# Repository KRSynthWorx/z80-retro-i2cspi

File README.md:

# [Z80-Retro!](https://github.com/johnwinans/2063-Z80) I2C/SPI Master Interface Board & Driver Library

An addon I2C/SPI master interface board that uses the [Z80-Retro!](https://github.com/johnwinans/2063-Z80)
parallel printer port and a bit-banged driver library to interact
with the I2C/SPI ports. KiCad design files are also included.

## Description

### Driver Library
[i2cspi_lib.asm](src/i2cspi_lib.asm) -
This driver library includes all necessary routines to communicate with I2C and SPI hardware devices
using the Z80-Retro! parallel port. Extensive comments and protocol descriptions are provided
to help understand the library. The library requires the [retromon.sym](https://github.com/KRSynthWorx/z80-retro-monitor/blob/main/src/retromon.sym)
symbol table from the [z80-retro-monitor](https://github.com/KRSynthWorx/z80-retro-monitor) project.

### PCB Hardware
An I2C/SPI master interface board using bit-bang techniques and utilizes the Z80-Retro!
parallel printer port. The PCB design includes 4 I2C ports and 4 SPI ports. The I2C
ports are all common and the SPI ports include 4 individual chip select (CS) lines.
Requires +5vdc be connected from the Z80-Retro! or an external power supply.

* A PDF version of the schematic can be found [here](kicad/i2c-adapter-schematic.pdf).
* Build of Materals (aka BOM) can be found [here](kicad/bom/ibom.html).

### PCB Layout

---

### I2C Timing Capture

---

### SPI Timing Capture

## Help

### Library Common Routines

```ACTIVE_LED``` - Set the ACTIVE LED on the I2C/SPI interface board on or off  

---

### I2C Routines

```I2C_INIT``` - Initialize I2C status variables and the Z80-Retro! PRN_DAT port  
```I2C_START``` - Initiate I2C communication with a START condition  
```I2C_STOP``` - Stop I2C communication with a STOP condition  
```I2C_SEND_BIT``` - Send a bit over the I2C bus  
```I2C_READ_BIT``` - Read a bit on the I2C bus  
```I2C_SEND_BYTE``` - Send a byte to the I2C bus  
```I2C_READ_BYTE``` - Read a byte from the I2C bus  
```I2C_SEND_STREAM``` - Send a byte stream to the I2C bus  
```I2C_READ_STREAM``` - Read a byte stream from the I2C bus  

---

### SPI Routines

```SPI_INIT```- Initialize the SPI MODE, bit transfer order and the Z80-Retro! PRN_DAT port  
```SPI_SEND_BYTE``` - Send 8 bits to the SPI port and discard the received data  
```SPI_READ_BYTE``` - Read 8 bits from the SPI port  
```SPI_CSx_TRUE``` - Assert the select line initialized in SPI_INIT (CS1 - CS4) supported  
```SPI_CSx_FALSE``` - De-assert the select line initialized in SPI_INIT (CS1 - CS4) supported  
```SPI_SEND_STREAM``` - Send a stream of bytes to the SPI port  
```SPI_READ_STREAM``` - Read a stream of bytes from the SPI port  

---

Several example routines are included to test the various functions. Everything is heavily
commented explaining the library routines and how to use them. These include:
- [ad_test.asm](src/ad_test.asm) - test a NXP Semiconductors PCF8591 I2C A/D-D/A converter
- [eeprom_test.asm](src/eeprom_test.asm) - test a generic 24C256 I2C EEPROM
- [gpio_test.asm](src/gpio_test.asm) - test a NXP Semiconductors PCF8574 I2C 8-bit GPIO expander
- [led_test.asm](src/led_test.asm) - test an Analog Devices MAX7219 LED driver in SPI mode 0
- [oled_test.asm](src/oled_test.asm) - test a generic SSD1306 128x64 SPI 0.96" OLED display
- [spi_test.asm](src/spi_test.asm) - test an Analog Devices ADXL345 accelerometer in SPI mode 3

## Author

[Kenny Maytum](mailto:ken_m@comcast.net) - KRSynthWorx

## Version History

* v1.0 - Driver Library
	* Initial Public Release
* v2.0 - KiCad Design Files
	* Initial Public Release

## License

This project is licensed under the [GNU Lesser General Public License] - see the LICENSE file for details

## Acknowledgments

Inspiration, code snippets, libraries, etc.
* [John's Basement YouTube Channel](https://www.youtube.com/c/JohnsBasement)
* [John Winans](https://github.com/johnwinans)
* [K. S. Jiang](https://github.com/ksjiang/bb85)
* [I2C Bus](https://i2c-bus.org)
* [SPI Bus](https://www.corelis.com/education/tutorials/spi-tutorial)

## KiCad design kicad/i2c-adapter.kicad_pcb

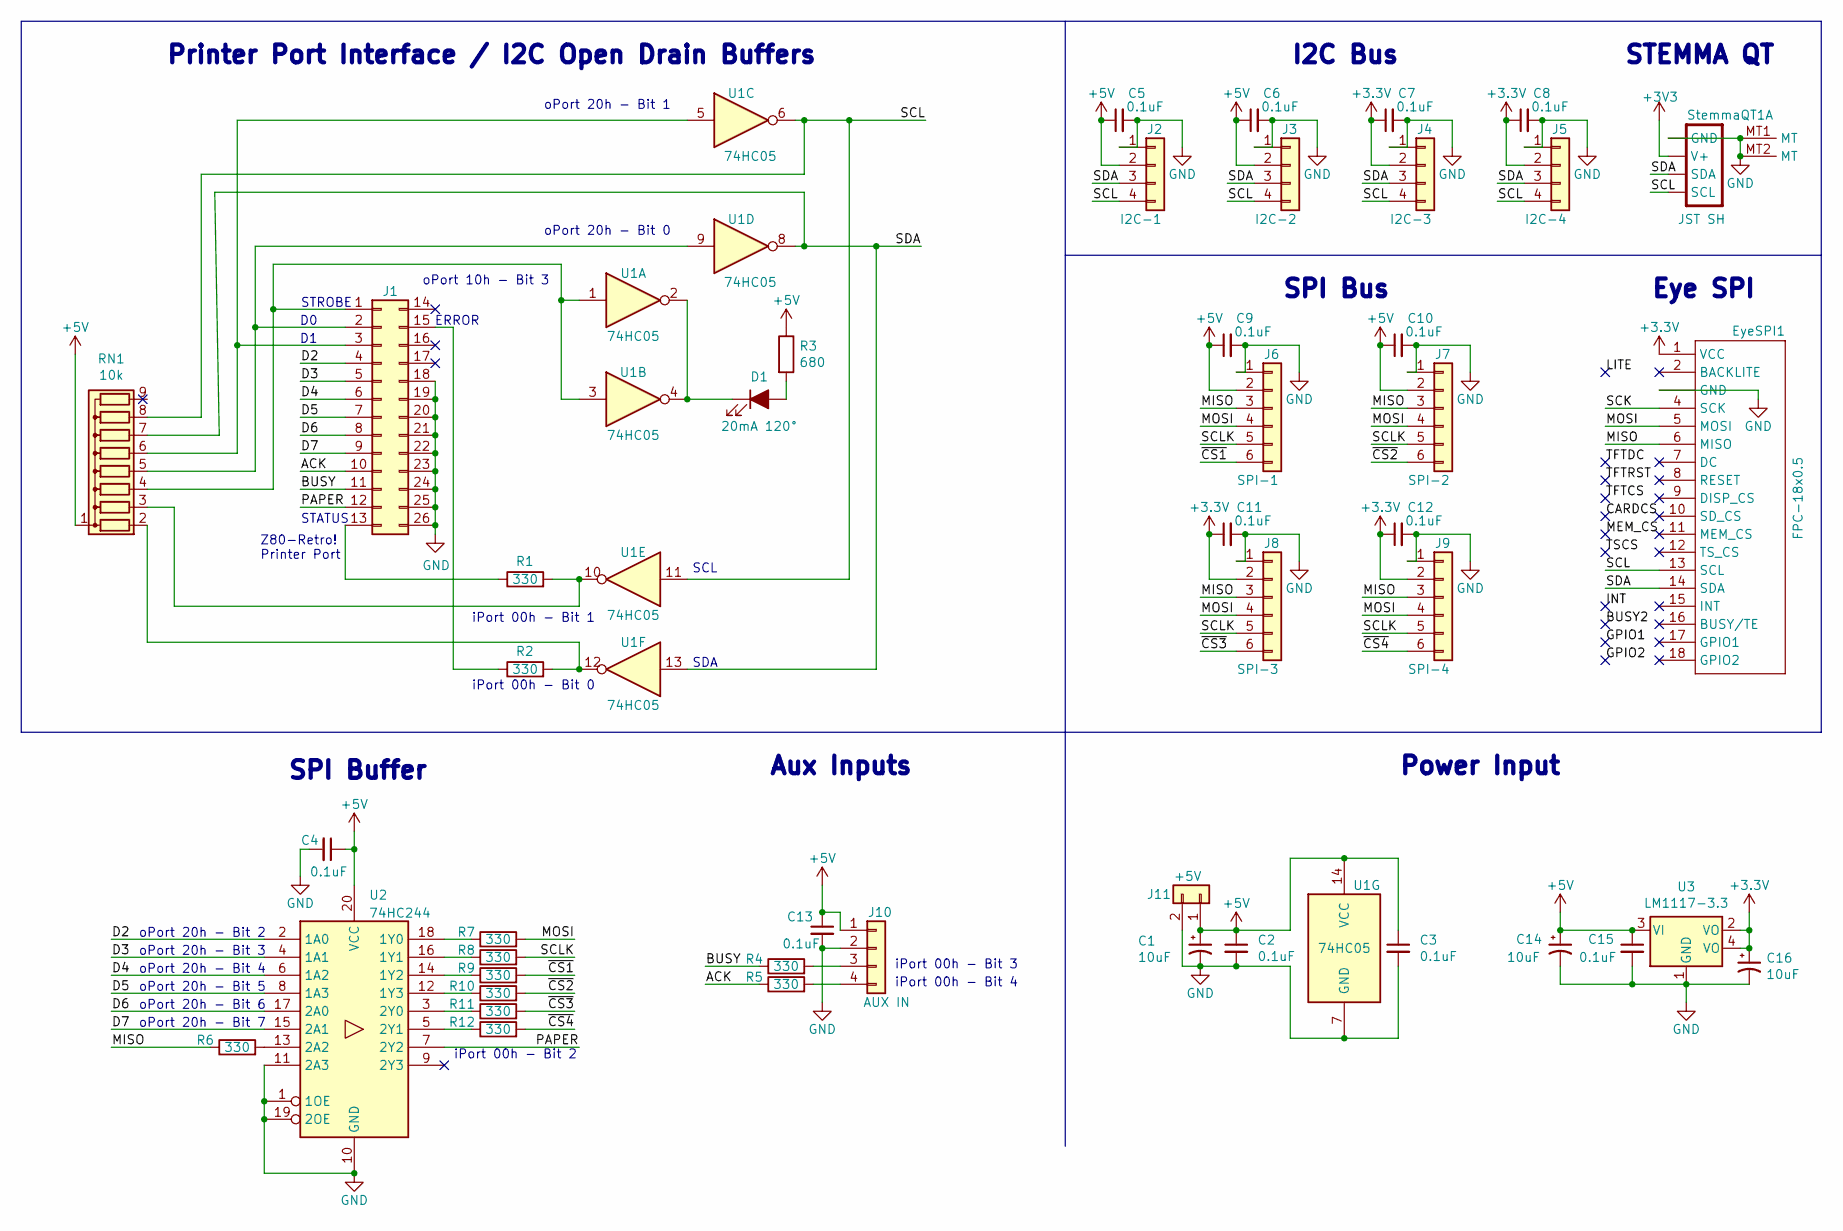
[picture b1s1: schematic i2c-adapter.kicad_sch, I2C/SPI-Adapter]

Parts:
C1: 10uF; CP_EIA-3216-10_Kemet-I_Pad1.58x1.35mm_HandSolder; LCSC C15850
C2, C3, C4, C5, C6, C7, C8, C9, C10, C11, C12, C13: 0.1uF; C_0805_2012Metric_Pad1.18x1.45mm_HandSolder; LCSC C28233
C14: 10uF; CP_EIA-3216-10_Kemet-I_Pad1.58x1.35mm_HandSolder; MPN ECE-A1EKS100; Digi-Key_PN P975-ND
C15: 0.1uF; C_0805_2012Metric_Pad1.18x1.45mm_HandSolder; MPN CL10B104KB8NNWC; Digi-Key_PN 1276-1935-1-ND
C16: 10uF; CP_EIA-3216-10_Kemet-I_Pad1.58x1.35mm_HandSolder; MPN CL21A106MQFNNNE; Digi-Key_PN 1276-1298-1-ND
D1: 20mA 120°; LED_0805_2012Metric_Pad1.15x1.40mm_HandSolder; LCSC C375546
EyeSPI1: FPC-18x0.5; EYE_SPI_DISPLAY_BOTCONTACT; LCSC C2856802
J1: Conn_02x13_Top_Bottom; PinSocket_2x13_P2.54mm_Vertical
J2: I2C-1; PinSocket_1x04_P2.54mm_Vertical
J3: I2C-2; PinSocket_1x04_P2.54mm_Vertical
J4: I2C-3; PinSocket_1x04_P2.54mm_Vertical
J5: I2C-4; PinSocket_1x04_P2.54mm_Vertical
J6: SPI-1; PinSocket_1x06_P2.54mm_Vertical
J7: SPI-2; PinSocket_1x06_P2.54mm_Vertical
J8: SPI-3; PinSocket_1x06_P2.54mm_Vertical
J9: SPI-4; PinSocket_1x06_P2.54mm_Vertical
J10: AUX IN; PinHeader_1x04_P2.54mm_Vertical
J11: +5V; PinHeader_1x02_P2.54mm_Vertical
R1, R2, R4, R5, R6, R7, R8, R9, R10, R11, R12: 330; R_0805_2012Metric_Pad1.20x1.40mm_HandSolder; LCSC C17630
R3: 680; R_0805_2012Metric_Pad1.20x1.40mm_HandSolder; LCSC C17798
RN1: 10k; R_Array_SIP9
StemmaQT1: JST SH; JST_SH4; LCSC C145956
U1: 74HC05; DIP-14_W7.62mm_Socket
U2: 74HC244; DIP-20_W7.62mm_Socket
U3: LM1117-3.3; SOT-223; MPN NCP1117ST33T3G; Digi-Key_PN NCP1117ST33T3GOSCT-ND

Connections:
+5V: C1.1, C2.1, C3.1, C4.1, C5.1, C6.1, C9.1, C10.1, C13.1, C14.1, C15.1, J2.2, J3.2, J6.2, J7.2, J10.1, J11.1, R3.1, RN1.1 (common), U1.14 (VCC), U2.20 (VCC), U3.3 (VI)
/ACK: J1.10, R5.1
/BUSY: J1.11, R4.1
/D2: J1.4, U2.2 (1A0)
/D3: J1.5, U2.4 (1A1)
/D4: J1.6, U2.6 (1A2)
/D5: J1.7, U2.8 (1A3)
/D6: J1.8, U2.17 (2A0)
/D7: J1.9, U2.15 (2A1)
/MISO: EyeSPI1.6 (MISO), J6.3, J7.3, J8.3, J9.3, R6.1
/MOSI: EyeSPI1.5 (MOSI), J6.4, J7.4, J8.4, J9.4, R7.2
/PAPER: J1.12, U2.7 (2Y2)
/SCK: EyeSPI1.4 (SCK)
/SCL: EyeSPI1.13 (SCL), J2.4, J3.4, J4.4, J5.4, RN1.8 (R7), StemmaQT1.4 (SCL), U1.6, U1.11
/SCLK: J6.5, J7.5, J8.5, J9.5, R8.2
/SDA: EyeSPI1.14 (SDA), J2.3, J3.3, J4.3, J5.3, RN1.7 (R6), StemmaQT1.3 (SDA), U1.8, U1.13
/~CS1: J6.6, R9.2
/~CS2: J7.6, R10.2
/~CS3: J8.6, R11.2
/~CS4: J9.6, R12.2
GND: C1.2, C2.2, C3.2, C4.2, C5.2, C6.2, C7.2, C8.2, C9.2, C10.2, C11.2, C12.2, C13.2, C14.2, C15.2, C16.2, EyeSPI1.3 (GND), EyeSPI1.SUPPORT1 (GND), EyeSPI1.SUPPORT2 (GND), J1.18, J1.19, J1.20, J1.21, J1.22, J1.23, J1.24, J1.25, J1.26, J2.1, J3.1, J4.1, J5.1, J6.1, J7.1, J8.1, J9.1, J10.2, J11.2, StemmaQT1.1 (GND), StemmaQT1.MT1 (MT), StemmaQT1.MT2 (MT), U1.7 (GND), U2.1 (1OE), U2.10 (GND), U2.11 (2A3), U2.19 (2OE), U3.1 (GND)
unnamed: D1.1 (K), U1.2, U1.4
unnamed: D1.2 (A), R3.2
unnamed: J1.1, RN1.4 (R3), U1.1, U1.3
unnamed: J1.2, RN1.5 (R4), U1.9
unnamed: J1.3, RN1.6 (R5), U1.5
unnamed: J1.13, R1.1
unnamed: J1.15, R2.1
unnamed: J10.3, R4.2
unnamed: J10.4, R5.2
unnamed: R1.2, RN1.3 (R2), U1.10
unnamed: R2.2, RN1.2 (R1), U1.12
unnamed: R6.2, U2.13 (2A2)
unnamed: R7.1, U2.18 (1Y0)
unnamed: R8.1, U2.16 (1Y1)
unnamed: R9.1, U2.14 (1Y2)
unnamed: R10.1, U2.12 (1Y3)
unnamed: R11.1, U2.3 (2Y0)
unnamed: R12.1, U2.5 (2Y1)

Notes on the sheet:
iPort 00h - Bit 0
oPort 20h - Bit 3
oPort 20h - Bit 5
oPort 20h - Bit 1
oPort 20h - Bit 0
oPort 10h - Bit 3
Printer Port Interface / I2C Open Drain Buffers
Z80-Retro! Printer Port
oPort 20h - Bit 2
ERROR
oPort 20h - Bit 7
oPort 20h - Bit 6
STATUS
I2C Bus
oPort 20h - Bit 4
SCL
STEMMA QT
Power Input
Aux Inputs
iPort 00h - Bit 4
Eye SPI
iPort 00h - Bit 3
iPort 00h - Bit 2
SDA
SPI Bus
STROBE
SPI Buffer
iPort 00h - Bit 1

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
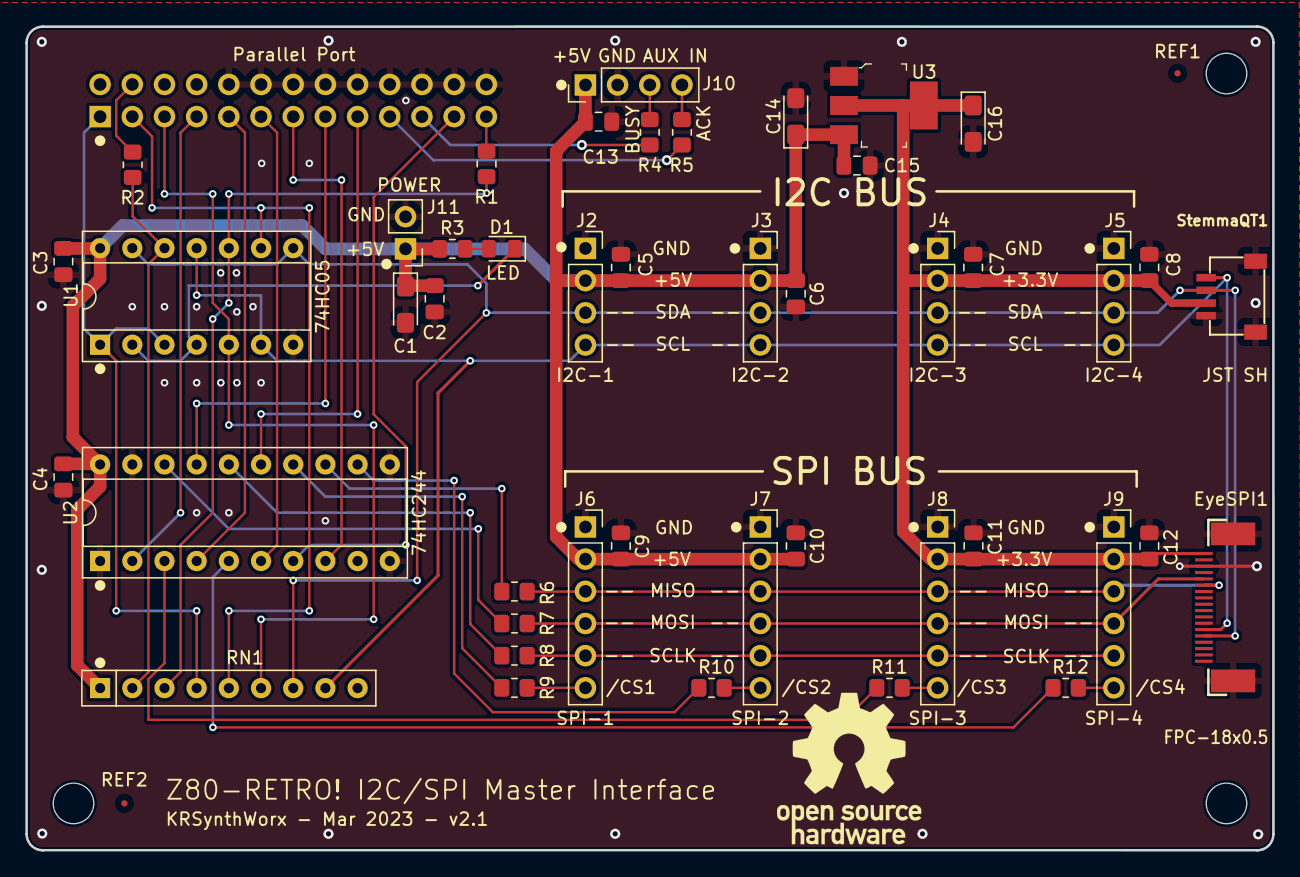
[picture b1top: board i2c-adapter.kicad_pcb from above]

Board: 2 copper layers, 98.4 x 65.0 mm, 48 parts (1 on the bottom side), 39 nets.

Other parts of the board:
REF1, REF2: Fiducial_0.5mm_Mask1.5mm

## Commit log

2022-10-24 Inital commit
2022-10-24 Update links
2022-10-25 Comment edit/add timing diagrams
2022-10-27 Add LED test example
2022-10-30 Add support for multiple 8x8 displays
2022-11-04 Add OLED display test example
2023-03-16 Cleaned up PCB routes and positions; Converted I2C to Adafruit standard pinout. Have Git ignore Kicad generated files.
2023-03-16 Add voltage regulator for +3.3V power; Move all SMD components to top side.
2023-03-17 Added BOM; Updated README to point to BOM Added JLCPCB SMD part references Specified LED characteristics (choose whichever color you want, default is RED) For jlcpcb/project.db, see https://github.co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
2023-03-17 We don't need the Kicad local preferences file in the Repo
2023-03-17 Added Adafruit compatible STEMMA QT I2C Connector and EyeSPI connector.
2023-03-17 Verified DRC and copper fill
2023-03-17 Finish up cleanup of both Schematic and PCB; Give Adafruit connectors labels.
2023-03-17 Update PCB Render
2023-03-17 Make the Adafruit connectors easier to understand; Label sockets with Chip Part #
